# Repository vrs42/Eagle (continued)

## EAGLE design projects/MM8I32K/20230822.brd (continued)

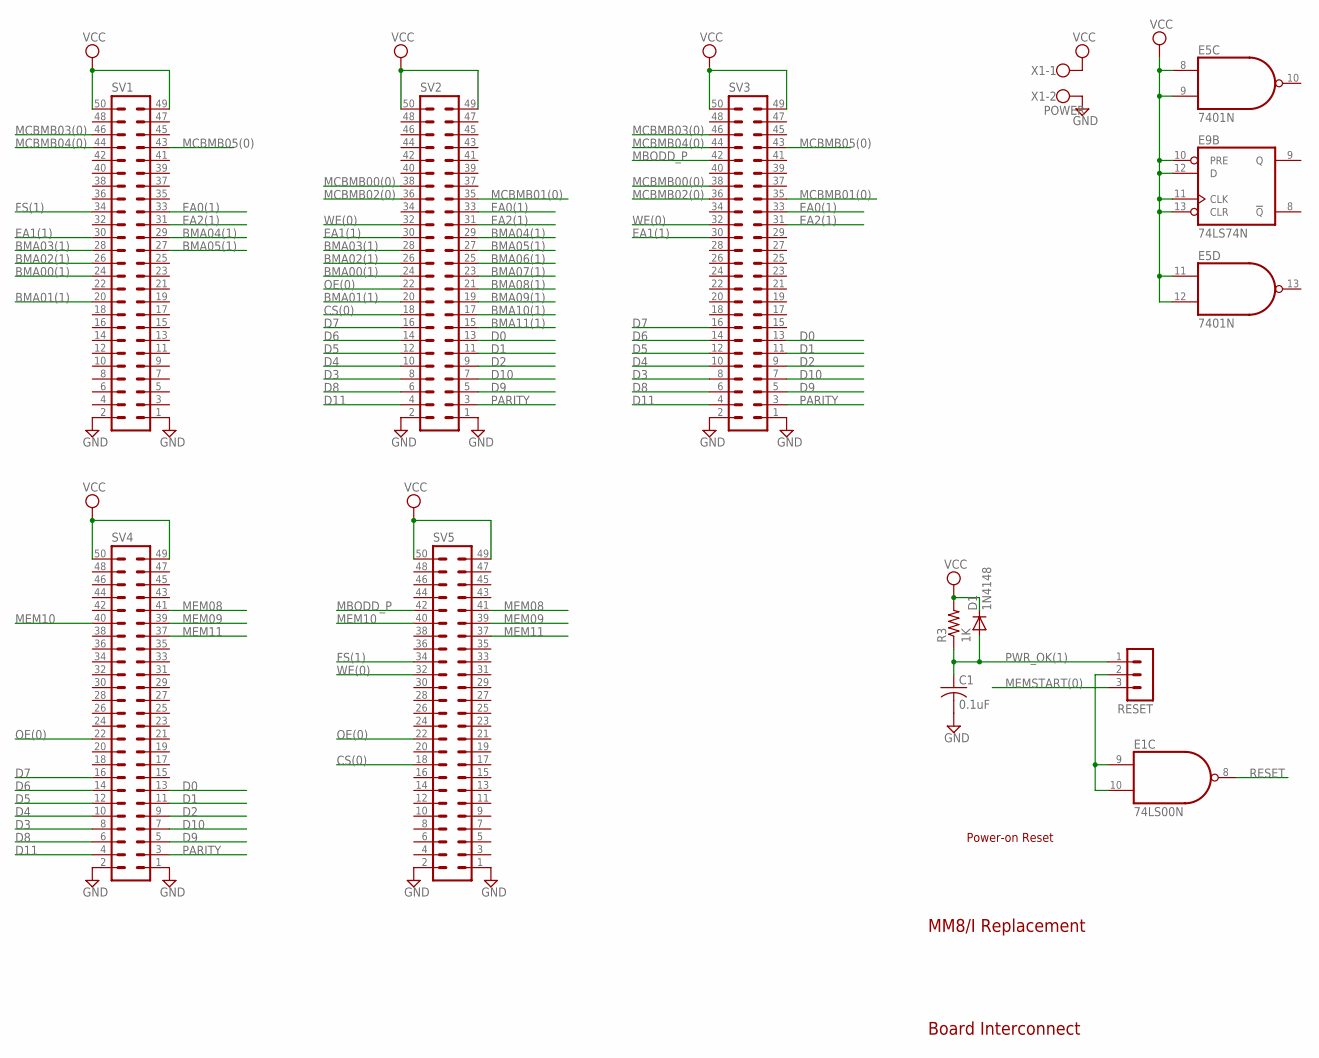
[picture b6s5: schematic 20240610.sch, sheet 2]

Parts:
C1: 0.1uF; C050-025X075
D1: 1N4148; DO35-10
E1: 74LS00N; DIL14
E5: 7401N; DIL14
E9: 74LS74N; DIL14
R3: 1K; 0207/10
RESET: MA03-1
SV1, SV2, SV3, SV4, SV5: ML50L
X1: POWER; W237-102

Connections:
BMA00(1): SV1.24, SV2.24; also elsewhere on the board
BMA01(1): SV1.20, SV2.20; also elsewhere on the board
BMA02(1): SV1.26, SV2.26; also elsewhere on the board
BMA03(1): SV1.28, SV2.28; also elsewhere on the board
BMA04(1): SV1.29, SV2.29; also elsewhere on the board
BMA05(1): SV1.27, SV2.27; also elsewhere on the board
BMA06(1): SV2.25; also elsewhere on the board
BMA07(1): SV2.23; also elsewhere on the board
BMA08(1): SV2.21; also elsewhere on the board
BMA09(1): SV2.19; also elsewhere on the board
BMA10(1): SV2.17; also elsewhere on the board
BMA11(1): SV2.15; also elsewhere on the board
CS(0): SV2.18, SV5.18; also elsewhere on the board
D0: SV2.13, SV3.13, SV4.13; also elsewhere on the board
D1: SV2.11, SV3.11, SV4.11; also elsewhere on the board
D2: SV2.9, SV3.9, SV4.9; also elsewhere on the board
D3: SV2.8, SV3.8, SV4.8; also elsewhere on the board
D4: SV2.10, SV3.10, SV4.10; also elsewhere on the board
D5: SV2.12, SV3.12, SV4.12; also elsewhere on the board
D6: SV2.14, SV3.14, SV4.14; also elsewhere on the board
D7: SV2.16, SV3.16, SV4.16; also elsewhere on the board
D8: SV2.6, SV3.6, SV4.6; also elsewhere on the board
D9: SV2.5, SV3.5, SV4.5; also elsewhere on the board
D10: SV2.7, SV3.7, SV4.7; also elsewhere on the board
D11: SV2.4, SV3.4, SV4.4; also elsewhere on the board
EA0(1): SV1.33, SV2.33, SV3.33; also elsewhere on the board
EA1(1): SV1.30, SV2.30, SV3.30; also elsewhere on the board
EA2(1): SV1.31, SV2.31, SV3.31; also elsewhere on the board
MBODD_P: SV3.42, SV5.42; also elsewhere on the board
MCBMB00(0): SV2.38, SV3.38; also elsewhere on the board
MCBMB01(0): SV2.35, SV3.35; also elsewhere on the board
MCBMB02(0): SV2.36, SV3.36; also elsewhere on the board
MCBMB03(0): SV1.46, SV3.46; also elsewhere on the board
MCBMB04(0): SV1.44, SV3.44; also elsewhere on the board
MCBMB05(0): SV1.43, SV3.43; also elsewhere on the board
MEM08: SV4.41, SV5.41; also elsewhere on the board
MEM09: SV4.39, SV5.39; also elsewhere on the board
MEM10: SV4.40, SV5.40; also elsewhere on the board
MEM11: SV4.37, SV5.37; also elsewhere on the board
MEMSTART(0): RESET.3; also elsewhere on the board
unnamed: E1.9 (I0), E1.10 (I1), RESET.2
OE(0): SV2.22, SV4.22, SV5.22; also elsewhere on the board
PARITY: SV2.3, SV3.3, SV4.3; also elsewhere on the board
WE(0): SV2.32, SV3.32, SV5.32; also elsewhere on the board

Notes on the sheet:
Board Interconnect
MM8/I Replacement
Power-on Reset

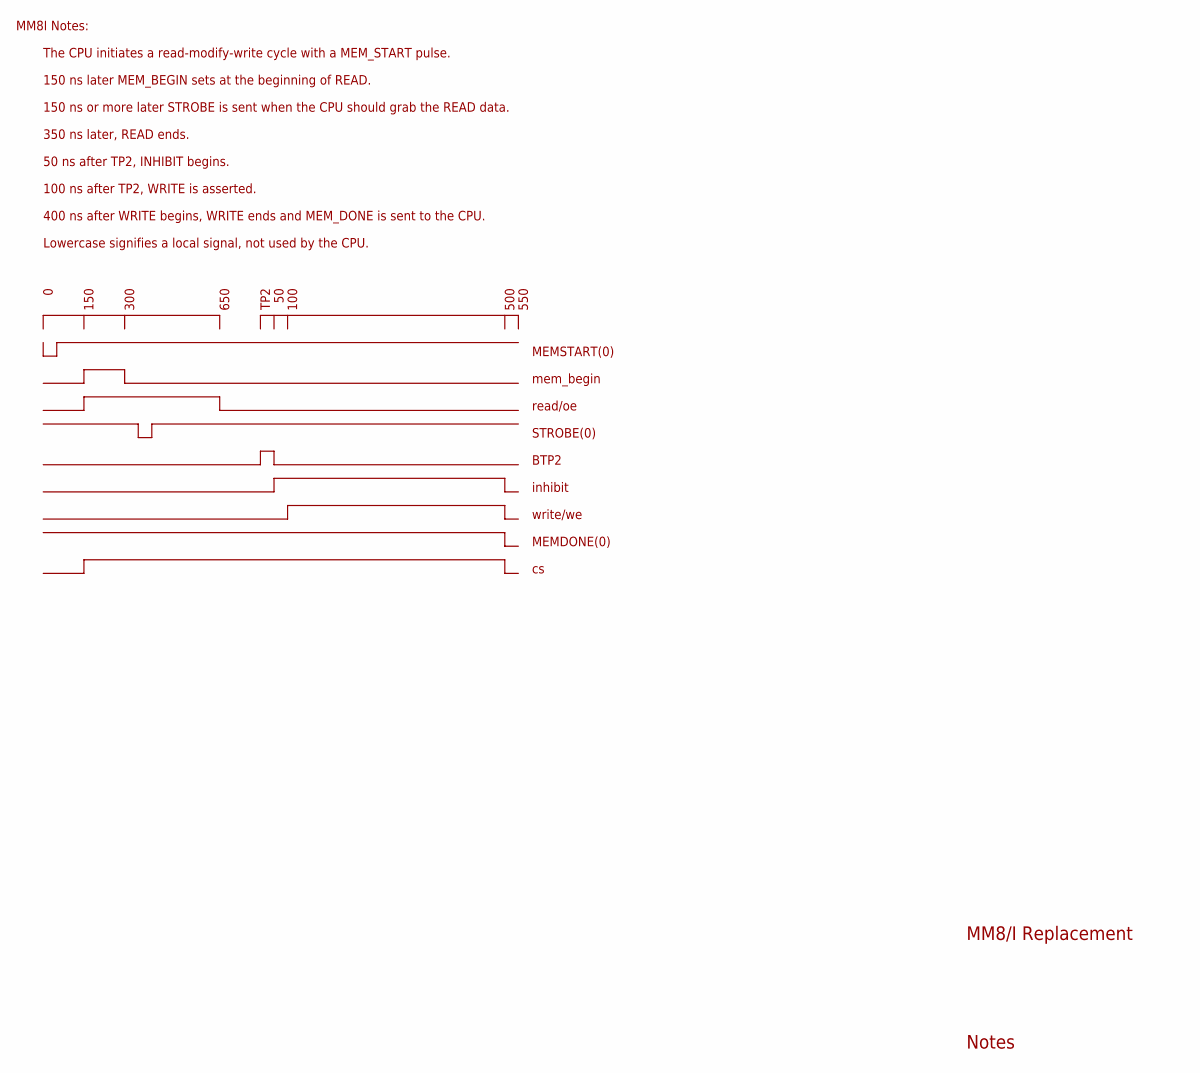
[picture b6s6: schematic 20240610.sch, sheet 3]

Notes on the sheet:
Notes
The CPU initiates a read-modify-write cycle with a MEM_START pulse.
150 ns later MEM_BEGIN sets at the beginning of READ.
150 ns or more later STROBE is sent when the CPU should grab the READ data.
50 ns after TP2, INHIBIT begins.
100 ns after TP2, WRITE is asserted.
400 ns after WRITE begins, WRITE ends and MEM_DONE is sent to the CPU.
350 ns later, READ ends.
150
300
650
TP2
100
500
MEMSTART(0)
mem_begin
read/oe
STROBE(0)
BTP2
inhibit
write/we
MEMDONE(0)
Lowercase signifies a local signal, not used by the CPU.
550
MM8I Notes:
MM8/I Replacement

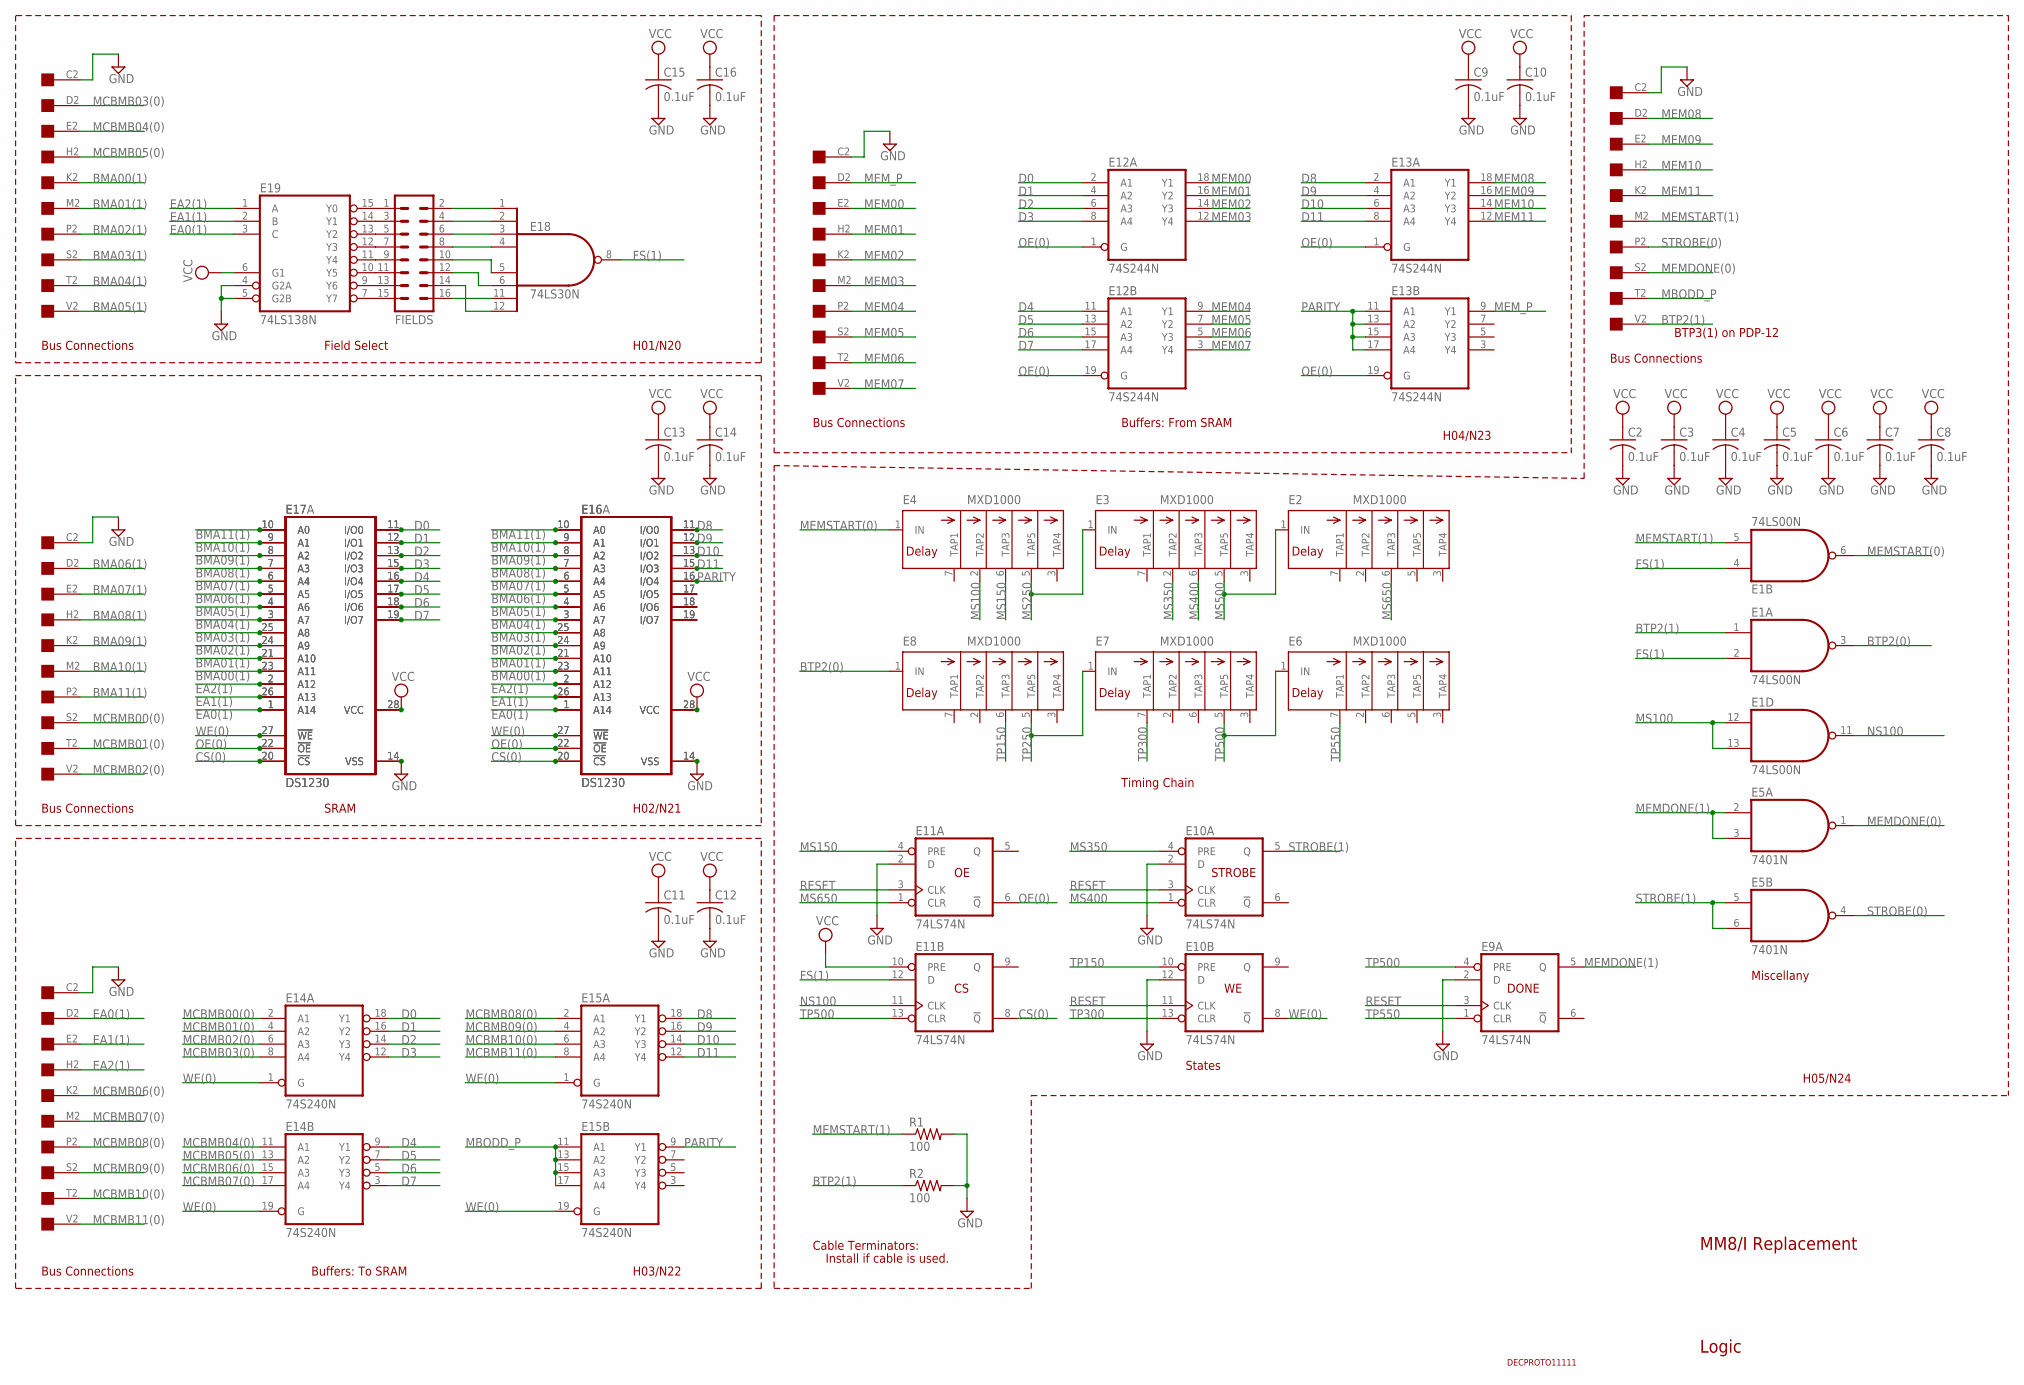
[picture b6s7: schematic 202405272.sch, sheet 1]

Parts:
C2, C3, C4, C5, C6, C7, C8, C9, C10, C11, C12, C13, C14, C15, C16: 0.1uF; C050-025X075
E1: 74LS00N; DIL14
E2, E3, E4, E6, E7, E8: MXD1000; DIL08
E5: 7401N; DIL14
E9, E10, E11: 74LS74N; DIL14
E12, E13: 74S244N; DIL20
E14, E15: 74S240N; DIL20
E16, E17: DS1230; DIL28-6
E16A, E17A: DS1230; DIL28-3
E18: 74LS30N; DIL14
E19: 74LS138N; DIL16
FIELDS: MA08-2
H01, H02, H03, H04, H05: EDGE-CON1
R1, R2: 100; 0207/10
U$6: DECPROTO11111

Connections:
BMA00(1): E16.23 (A11), E16A.23 (A11), E17.23 (A11), E17A.23 (A11), H01.K2; also elsewhere on the board
BMA01(1): E16.21 (A10), E16A.21 (A10), E17.21 (A10), E17A.21 (A10), H01.M2; also elsewhere on the board
BMA02(1): E16.24 (A9), E16A.24 (A9), E17.24 (A9), E17A.24 (A9), H01.P2; also elsewhere on the board
BMA03(1): E16.25 (A8), E16A.25 (A8), E17.25 (A8), E17A.25 (A8), H01.S2; also elsewhere on the board
BMA04(1): E16.3 (A7), E16A.3 (A7), E17.3 (A7), E17A.3 (A7), H01.T2; also elsewhere on the board
BMA05(1): E16.4 (A6), E16A.4 (A6), E17.4 (A6), E17A.4 (A6), H01.V2; also elsewhere on the board
BMA06(1): E16.5 (A5), E16A.5 (A5), E17.5 (A5), E17A.5 (A5), H02.D2; also elsewhere on the board
BMA07(1): E16.6 (A4), E16A.6 (A4), E17.6 (A4), E17A.6 (A4), H02.E2; also elsewhere on the board
BMA08(1): E16.7 (A3), E16A.7 (A3), E17.7 (A3), E17A.7 (A3), H02.H2; also elsewhere on the board
BMA09(1): E16.8 (A2), E16A.8 (A2), E17.8 (A2), E17A.8 (A2), H02.K2; also elsewhere on the board
BMA10(1): E16.9 (A1), E16A.9 (A1), E17.9 (A1), E17A.9 (A1), H02.M2; also elsewhere on the board
BMA11(1): E16.10 (A0), E16A.10 (A0), E17.10 (A0), E17A.10 (A0), H02.P2; also elsewhere on the board
BTP2(0): E1.3 (O), E8.1 (IN); also elsewhere on the board
BTP2(1): E1.1 (I0), H05.V2, R2.1
CS(0): E11.8 (!Q), E16.20 (!CS), E16A.20 (!CS), E17.20 (!CS), E17A.20 (!CS); also elsewhere on the board
D0: E12.2 (A1), E14.18 (Y1), E17.11 (I/O0), E17A.11 (I/O0); also elsewhere on the board
D1: E12.4 (A2), E14.16 (Y2), E17.12 (I/O1), E17A.12 (I/O1); also elsewhere on the board
D2: E12.6 (A3), E14.14 (Y3), E17.13 (I/O2), E17A.13 (I/O2); also elsewhere on the board
D3: E12.8 (A4), E14.12 (Y4), E17.15 (I/O3), E17A.15 (I/O3); also elsewhere on the board
D4: E12.11 (A1), E14.9 (Y1), E17.16 (I/O4), E17A.16 (I/O4); also elsewhere on the board
D5: E12.13 (A2), E14.7 (Y2), E17.17 (I/O5), E17A.17 (I/O5); also elsewhere on the board
D6: E12.15 (A3), E14.5 (Y3), E17.18 (I/O6), E17A.18 (I/O6); also elsewhere on the board
D7: E12.17 (A4), E14.3 (Y4), E17.19 (I/O7), E17A.19 (I/O7); also elsewhere on the board
D8: E13.2 (A1), E15.18 (Y1), E16.11 (I/O0), E16A.11 (I/O0); also elsewhere on the board
D9: E13.4 (A2), E15.16 (Y2), E16.12 (I/O1), E16A.12 (I/O1); also elsewhere on the board
D10: E13.6 (A3), E15.14 (Y3), E16.13 (I/O2), E16A.13 (I/O2); also elsewhere on the board
D11: E13.8 (A4), E15.12 (Y4), E16.15 (I/O3), E16A.15 (I/O3); also elsewhere on the board
EA0(1): E16.1 (A14), E16A.1 (A14), E17.1 (A14), E17A.1 (A14), E19.3 (C), H03.D2; also elsewhere on the board
EA1(1): E16.26 (A13), E16A.26 (A13), E17.26 (A13), E17A.26 (A13), E19.2 (B), H03.E2; also elsewhere on the board
EA2(1): E16.2 (A12), E16A.2 (A12), E17.2 (A12), E17A.2 (A12), E19.1 (A), H03.H2; also elsewhere on the board
MBODD_P: E15.11 (A1), E15.13 (A2), E15.15 (A3), E15.17 (A4), H05.T2; also elsewhere on the board
MCBMB00(0): E14.2 (A1), H02.S2; also elsewhere on the board
MCBMB01(0): E14.4 (A2), H02.T2; also elsewhere on the board
MCBMB02(0): E14.6 (A3), H02.V2; also elsewhere on the board
MCBMB03(0): E14.8 (A4), H01.D2; also elsewhere on the board
MCBMB04(0): E14.11 (A1), H01.E2; also elsewhere on the board
MCBMB05(0): E14.13 (A2), H01.H2; also elsewhere on the board
MCBMB06(0): E14.15 (A3), H03.K2
MCBMB07(0): E14.17 (A4), H03.M2
MCBMB08(0): E15.2 (A1), H03.P2
MCBMB09(0): E15.4 (A2), H03.S2
MCBMB10(0): E15.6 (A3), H03.T2
MCBMB11(0): E15.8 (A4), H03.V2
MEM00: E12.18 (Y1), H04.E2
MEM01: E12.16 (Y2), H04.H2
MEM02: E12.14 (Y3), H04.K2
MEM03: E12.12 (Y4), H04.M2
MEM04: E12.9 (Y1), H04.P2
MEM05: E12.7 (Y2), H04.S2
MEM06: E12.5 (Y3), H04.T2
MEM07: E12.3 (Y4), H04.V2
MEM08: E13.18 (Y1), H05.D2; also elsewhere on the board
MEM09: E13.16 (Y2), H05.E2; also elsewhere on the board
MEM10: E13.14 (Y3), H05.H2; also elsewhere on the board
MEM11: E13.12 (Y4), H05.K2; also elsewhere on the board
MEMDONE(0): E5.1 (O), H05.S2
MEMDONE(1): E5.2 (I0), E5.3 (I1), E9.5 (Q); also elsewhere on the board
MEMSTART(0): E1.6 (O), E4.1 (IN); also elsewhere on the board
MEMSTART(1): E1.5 (I1), H05.M2, R1.1
MEM_P: E13.9 (Y1), H04.D2
MS100: E1.12 (I0), E1.13 (I1), E4.2 (TAP2)
MS150: E4.6 (TAP3), E11.4 (PRE)
MS250: E3.1 (IN), E4.5 (TAP5)
MS350: E3.2 (TAP2), E10.4 (PRE)
MS400: E3.6 (TAP3), E10.1 (CLR)
MS500: E2.1 (IN), E3.5 (TAP5)
MS650: E2.6 (TAP3), E11.1 (CLR)
unnamed: E19.15 (Y0), FIELDS.1
unnamed: E19.14 (Y1), FIELDS.3
unnamed: E19.13 (Y2), FIELDS.5
unnamed: E19.12 (Y3), FIELDS.7
unnamed: E19.11 (Y4), FIELDS.9
unnamed: E19.10 (Y5), FIELDS.11
unnamed: E19.9 (Y6), FIELDS.13
unnamed: E19.7 (Y7), FIELDS.15
unnamed: E18.4 (I3), FIELDS.8
unnamed: E18.3 (I2), FIELDS.6
unnamed: E18.2 (I1), FIELDS.4
unnamed: E18.1 (I0), FIELDS.2
unnamed: E18.5 (I4), FIELDS.10
unnamed: E18.6 (I5), FIELDS.12
unnamed: E18.12 (I7), FIELDS.14
unnamed: E18.11 (I6), FIELDS.16
unnamed: E16.17 (I/O5), E16A.17 (I/O5)
unnamed: E16.18 (I/O6), E16A.18 (I/O6)
unnamed: E16.19 (I/O7), E16A.19 (I/O7)
OE(0): E11.6 (!Q), E12.1 (G), E12.19 (G), E13.1 (G), E13.19 (G), E16.22 (!OE), E16A.22 (!OE), E17.22 (!OE), E17A.22 (!OE); also elsewhere on the board
PARITY: E13.11 (A1), E13.13 (A2), E13.15 (A3), E13.17 (A4), E15.9 (Y1), E16.16 (I/O4), E16A.16 (I/O4); also elsewhere on the board
STROBE(0): E5.4 (O), H05.P2
STROBE(1): E5.5 (I0), E5.6 (I1), E10.5 (Q); also elsewhere on the board
TP150: E8.6 (TAP3), E10.10 (PRE)
TP250: E7.1 (IN), E8.5 (TAP5)
TP300: E7.7 (TAP1), E10.13 (CLR)
WE(0): E10.8 (!Q), E14.1 (G), E14.19 (G), E15.1 (G), E15.19 (G), E16.27 (!WE), E16A.27 (!WE), E17.27 (!WE), E17A.27 (!WE); also elsewhere on the board

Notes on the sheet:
STROBE
DONE
H01/N20
H02/N21
H03/N22
H04/N23
Field Select
SRAM
MM8/I Replacement
Buffers: To SRAM
Buffers: From SRAM
Timing Chain
States
BTP3(1) on PDP-12
Miscellany
H05/N24
Logic
Bus Connections
Cable Terminators:
Install if cable is used.

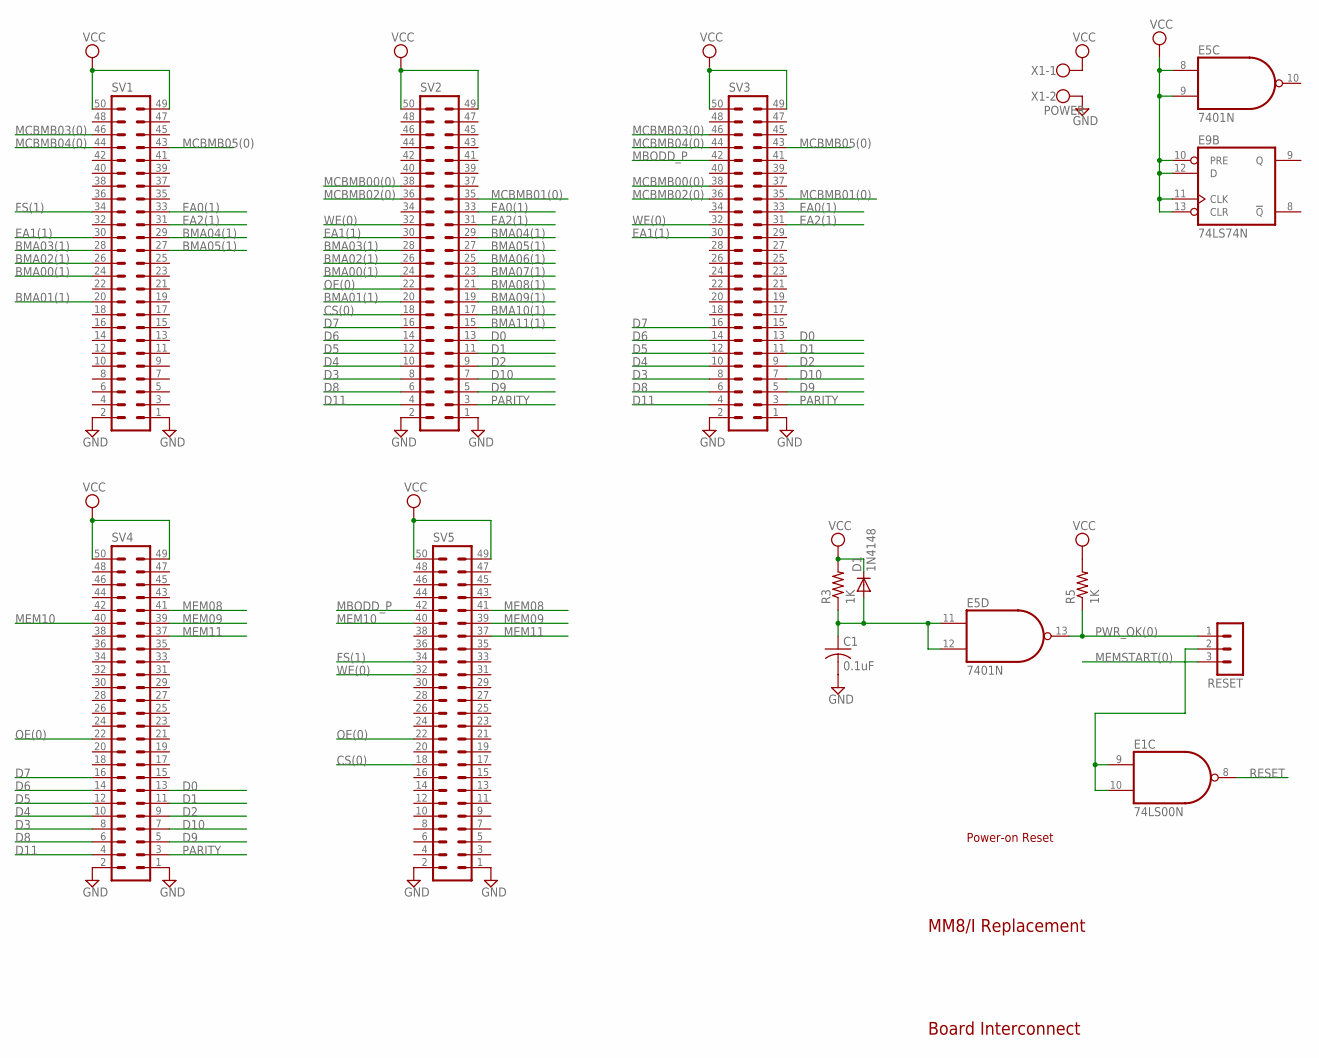
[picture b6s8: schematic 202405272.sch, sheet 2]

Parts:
C1: 0.1uF; C050-025X075
D1: 1N4148; DO35-10
E1: 74LS00N; DIL14
E5: 7401N; DIL14
E9: 74LS74N; DIL14
R3, R5: 1K; 0207/10
RESET: MA03-1
SV1, SV2, SV3, SV4, SV5: ML50L
X1: POWER; W237-102

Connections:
BMA00(1): SV1.24, SV2.24; also elsewhere on the board
BMA01(1): SV1.20, SV2.20; also elsewhere on the board
BMA02(1): SV1.26, SV2.26; also elsewhere on the board
BMA03(1): SV1.28, SV2.28; also elsewhere on the board
BMA04(1): SV1.29, SV2.29; also elsewhere on the board
BMA05(1): SV1.27, SV2.27; also elsewhere on the board
BMA06(1): SV2.25; also elsewhere on the board
BMA07(1): SV2.23; also elsewhere on the board
BMA08(1): SV2.21; also elsewhere on the board
BMA09(1): SV2.19; also elsewhere on the board
BMA10(1): SV2.17; also elsewhere on the board
BMA11(1): SV2.15; also elsewhere on the board
CS(0): SV2.18, SV5.18; also elsewhere on the board
D0: SV2.13, SV3.13, SV4.13; also elsewhere on the board
D1: SV2.11, SV3.11, SV4.11; also elsewhere on the board
D2: SV2.9, SV3.9, SV4.9; also elsewhere on the board
D3: SV2.8, SV3.8, SV4.8; also elsewhere on the board
D4: SV2.10, SV3.10, SV4.10; also elsewhere on the board
D5: SV2.12, SV3.12, SV4.12; also elsewhere on the board
D6: SV2.14, SV3.14, SV4.14; also elsewhere on the board
D7: SV2.16, SV3.16, SV4.16; also elsewhere on the board
D8: SV2.6, SV3.6, SV4.6; also elsewhere on the board
D9: SV2.5, SV3.5, SV4.5; also elsewhere on the board
D10: SV2.7, SV3.7, SV4.7; also elsewhere on the board
D11: SV2.4, SV3.4, SV4.4; also elsewhere on the board
EA0(1): SV1.33, SV2.33, SV3.33; also elsewhere on the board
EA1(1): SV1.30, SV2.30, SV3.30; also elsewhere on the board
EA2(1): SV1.31, SV2.31, SV3.31; also elsewhere on the board
MBODD_P: SV3.42, SV5.42; also elsewhere on the board
MCBMB00(0): SV2.38, SV3.38; also elsewhere on the board
MCBMB01(0): SV2.35, SV3.35; also elsewhere on the board
MCBMB02(0): SV2.36, SV3.36; also elsewhere on the board
MCBMB03(0): SV1.46, SV3.46; also elsewhere on the board
MCBMB04(0): SV1.44, SV3.44; also elsewhere on the board
MCBMB05(0): SV1.43, SV3.43; also elsewhere on the board
MEM08: SV4.41, SV5.41; also elsewhere on the board
MEM09: SV4.39, SV5.39; also elsewhere on the board
MEM10: SV4.40, SV5.40; also elsewhere on the board
MEM11: SV4.37, SV5.37; also elsewhere on the board
MEMSTART(0): RESET.3; also elsewhere on the board
unnamed: E1.9 (I0), E1.10 (I1), RESET.2
OE(0): SV2.22, SV4.22, SV5.22; also elsewhere on the board
PARITY: SV2.3, SV3.3, SV4.3; also elsewhere on the board
WE(0): SV2.32, SV3.32, SV5.32; also elsewhere on the board

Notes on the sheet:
Board Interconnect
MM8/I Replacement
Power-on Reset

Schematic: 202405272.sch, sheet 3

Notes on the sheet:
Notes
The CPU initiates a read-modify-write cycle with a MEM_START pulse.
150 ns later MEM_BEGIN sets at the beginning of READ.
150 ns or more later STROBE is sent when the CPU should grab the READ data.
50 ns after TP2, INHIBIT begins.
100 ns after TP2, WRITE is asserted.
400 ns after WRITE begins, WRITE ends and MEM_DONE is sent to the CPU.
350 ns later, READ ends.
150
300
650
TP2
100
500
MEMSTART(0)
mem_begin
read/oe
STROBE(0)
BTP2
inhibit
write/we
MEMDONE(0)
Lowercase signifies a local signal, not used by the CPU.
550
MM8I Notes:
MM8/I Replacement

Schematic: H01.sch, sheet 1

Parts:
C15, C16: 0.1uF; C050-025X075
E18: 74LS30N; DIL14
E19: 74LS138N; DIL16
FIELDS: MA08-2
H01: EDGE-CON1
U$6: DECPROTO11111

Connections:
BMA00(1): H01.K2; also elsewhere on the board
BMA01(1): H01.M2; also elsewhere on the board
BMA02(1): H01.P2; also elsewhere on the board
BMA03(1): H01.S2; also elsewhere on the board
BMA04(1): H01.T2; also elsewhere on the board
BMA05(1): H01.V2; also elsewhere on the board
EA0(1): E19.3 (C); also elsewhere on the board
EA1(1): E19.2 (B); also elsewhere on the board
EA2(1): E19.1 (A); also elsewhere on the board
MCBMB03(0): H01.D2; also elsewhere on the board
MCBMB04(0): H01.E2; also elsewhere on the board
MCBMB05(0): H01.H2; also elsewhere on the board
unnamed: E19.15 (Y0), FIELDS.1
unnamed: E19.14 (Y1), FIELDS.3
unnamed: E19.13 (Y2), FIELDS.5
unnamed: E19.12 (Y3), FIELDS.7
unnamed: E19.11 (Y4), FIELDS.9
unnamed: E19.10 (Y5), FIELDS.11
unnamed: E19.9 (Y6), FIELDS.13
unnamed: E19.7 (Y7), FIELDS.15
unnamed: E18.4 (I3), FIELDS.8
unnamed: E18.3 (I2), FIELDS.6
unnamed: E18.2 (I1), FIELDS.4
unnamed: E18.1 (I0), FIELDS.2
unnamed: E18.5 (I4), FIELDS.10
unnamed: E18.6 (I5), FIELDS.12
unnamed: E18.12 (I7), FIELDS.14
unnamed: E18.11 (I6), FIELDS.16

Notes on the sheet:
H01/N20
Field Select
MM8/I Replacement
Logic
Bus Connections

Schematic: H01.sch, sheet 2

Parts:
SV1: ML50L
X1: POWER; W237-102

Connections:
BMA00(1): SV1.24; also elsewhere on the board
BMA01(1): SV1.20; also elsewhere on the board
BMA02(1): SV1.26; also elsewhere on the board
BMA03(1): SV1.28; also elsewhere on the board
BMA04(1): SV1.29; also elsewhere on the board
BMA05(1): SV1.27; also elsewhere on the board
EA0(1): SV1.33; also elsewhere on the board
EA1(1): SV1.30; also elsewhere on the board
EA2(1): SV1.31; also elsewhere on the board
MCBMB03(0): SV1.46; also elsewhere on the board
MCBMB04(0): SV1.44; also elsewhere on the board
MCBMB05(0): SV1.43; also elsewhere on the board

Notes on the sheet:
Board Interconnect
MM8/I Replacement

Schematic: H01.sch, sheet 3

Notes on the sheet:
Notes
The CPU initiates a read-modify-write cycle with a MEM_START pulse.
150 ns later MEM_BEGIN sets at the beginning of READ.
150 ns or more later STROBE is sent when the CPU should grab the READ data.
50 ns after TP2, INHIBIT begins.
100 ns after TP2, WRITE is asserted.
400 ns after WRITE begins, WRITE ends and MEM_DONE is sent to the CPU.
350 ns later, READ ends.
150
300
650
TP2
100
500
MEMSTART(0)
mem_begin
read/oe
STROBE(0)
BTP2
inhibit
write/we
MEMDONE(0)
Lowercase signifies a local signal, not used by the CPU.
550
MM8I Notes:
MM8/I Replacement

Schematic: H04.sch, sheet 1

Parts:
C9, C10: 0.1uF; C050-025X075
E12, E13: 74S244N; DIL20
H04: EDGE-CON1
U$6: DECPROTO11111

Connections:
D0: E12.2 (A1); also elsewhere on the board
D1: E12.4 (A2); also elsewhere on the board
D2: E12.6 (A3); also elsewhere on the board
D3: E12.8 (A4); also elsewhere on the board
D4: E12.11 (A1); also elsewhere on the board
D5: E12.13 (A2); also elsewhere on the board
D6: E12.15 (A3); also elsewhere on the board
D7: E12.17 (A4); also elsewhere on the board
D8: E13.2 (A1); also elsewhere on the board
D9: E13.4 (A2); also elsewhere on the board
D10: E13.6 (A3); also elsewhere on the board
D11: E13.8 (A4); also elsewhere on the board
MEM00: E12.18 (Y1), H04.E2
MEM01: E12.16 (Y2), H04.H2
MEM02: E12.14 (Y3), H04.K2
MEM03: E12.12 (Y4), H04.M2
MEM04: E12.9 (Y1), H04.P2
MEM05: E12.7 (Y2), H04.S2
MEM06: E12.5 (Y3), H04.T2
MEM07: E12.3 (Y4), H04.V2
MEM08: E13.18 (Y1); also elsewhere on the board
MEM09: E13.16 (Y2); also elsewhere on the board
MEM10: E13.14 (Y3); also elsewhere on the board
MEM11: E13.12 (Y4); also elsewhere on the board
MEM_P: E13.9 (Y1), H04.D2
OE(0): E12.1 (G), E12.19 (G), E13.1 (G), E13.19 (G); also elsewhere on the board
PARITY: E13.11 (A1), E13.13 (A2), E13.15 (A3), E13.17 (A4); also elsewhere on the board

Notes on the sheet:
H04/N23
MM8/I Replacement
Buffers: From SRAM
Logic
Bus Connections

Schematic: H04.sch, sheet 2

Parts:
SV4: ML50L

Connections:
D0: SV4.13; also elsewhere on the board
D1: SV4.11; also elsewhere on the board
D2: SV4.9; also elsewhere on the board
D3: SV4.8; also elsewhere on the board
D4: SV4.10; also elsewhere on the board
D5: SV4.12; also elsewhere on the board
D6: SV4.14; also elsewhere on the board
D7: SV4.16; also elsewhere on the board
D8: SV4.6; also elsewhere on the board
D9: SV4.5; also elsewhere on the board
D10: SV4.7; also elsewhere on the board
D11: SV4.4; also elsewhere on the board
MEM08: SV4.41; also elsewhere on the board
MEM09: SV4.39; also elsewhere on the board
MEM10: SV4.40; also elsewhere on the board
MEM11: SV4.37; also elsewhere on the board
OE(0): SV4.22; also elsewhere on the board
PARITY: SV4.3; also elsewhere on the board

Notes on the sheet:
Board Interconnect
MM8/I Replacement

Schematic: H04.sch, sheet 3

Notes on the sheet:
Notes
The CPU initiates a read-modify-write cycle with a MEM_START pulse.
150 ns later MEM_BEGIN sets at the beginning of READ.
150 ns or more later STROBE is sent when the CPU should grab the READ data.
50 ns after TP2, INHIBIT begins.
100 ns after TP2, WRITE is asserted.
400 ns after WRITE begins, WRITE ends and MEM_DONE is sent to the CPU.
350 ns later, READ ends.
150
300
650
TP2
100
500
MEMSTART(0)
mem_begin
read/oe
STROBE(0)
BTP2
inhibit
write/we
MEMDONE(0)
Lowercase signifies a local signal, not used by the CPU.
550
MM8I Notes:
MM8/I Replacement

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
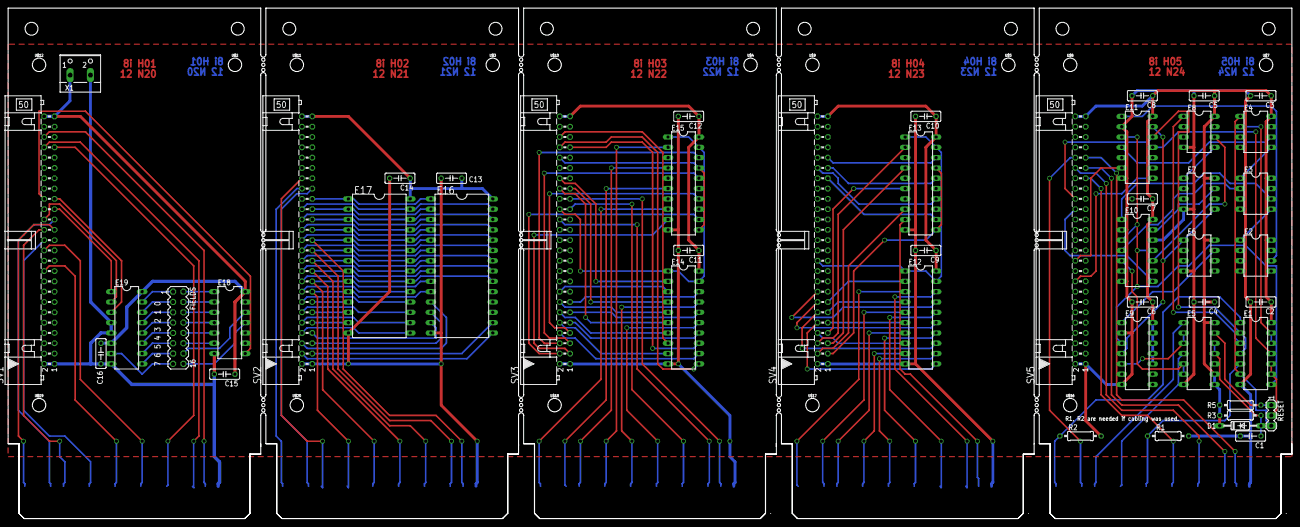
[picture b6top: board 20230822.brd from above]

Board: 2 copper layers, 316.2 x 125.7 mm, 69 parts (0 on the bottom side), 101 nets.

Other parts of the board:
U$2, U$3, U$4, U$5, U$7, U$8, U$9, U$10, U$11, U$12, U$16, U$17, U$18, U$19, U$20: STAND-OFF

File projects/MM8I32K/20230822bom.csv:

Qty,Value,Device,Package,Parts,Description
5, ,EDGE-1,EDGE-CON1,"H01, H02, H03, H04, H05",Single-Sided DEC Edge Connector -- (side 2)
1, ,MA03-1,MA03-1,RESET,PIN HEADER
1, ,MA08-2,MA08-2,FIELDS,PIN HEADER
5, ,ML50L,ML50L,"SV1, SV2, SV3, SV4, SV5",HARTING
16,0.1uF,C-US050-025X075,C050-025X075,"C1, C2, C3, C4, C5, C6, C7, C8, C9, C10, C11, C12, C13, C14, C15, C16","CAPACITOR, American symbol"
2,100,R-US_0207/10,0207/10,"R1, R2","RESISTOR, American symbol"
2,1K,R-US_0207/10,0207/10,"R3, R5","RESISTOR, American symbol"
1,1N4148,1N4148DO35-10,DO35-10,D1,DIODE
1,74LS00N,74LS00N,DIL14,E1,Quad 2-input NAND gate
1,74LS01N,74LS01N,DIL14,E5,"Quad 2-input NAND gate, open collector"
1,74LS138N,74LS138N,DIL16,E19,3-line to 8-line DECODER/DEMULTIPLEXER
1,74LS30N,74LS30N,DIL14,E18,8-input NAND gate
3,74LS74N,74LS74N,DIL14,"E9, E10, E11","Dual D type positive edge triggered FLIP FLOP, preset and clear"
2,74S240N,74S240N,DIL20,"E14, E15","Octal BUFFER and LINE DRIVER, 3-state"
2,74S244N,74S244N,DIL20,"E12, E13","Octal BUFFER and LINE DRIVER, 3-state"
1,DECPROTO11111,DECPROTO11111,DECPROTO11111,U$6,Various small DEC boards stuck together with break-away tab routing.
2,DS1230,62256P,DIL28-6,"E16, E17",MEMORY
6,MXD1000,MXD1000,DIL08,"E2, E3, E4, E6, E7, E8",DELAY LINE
1,POWER,W237-102,W237-102,X1,WAGO SCREW CLAMP
